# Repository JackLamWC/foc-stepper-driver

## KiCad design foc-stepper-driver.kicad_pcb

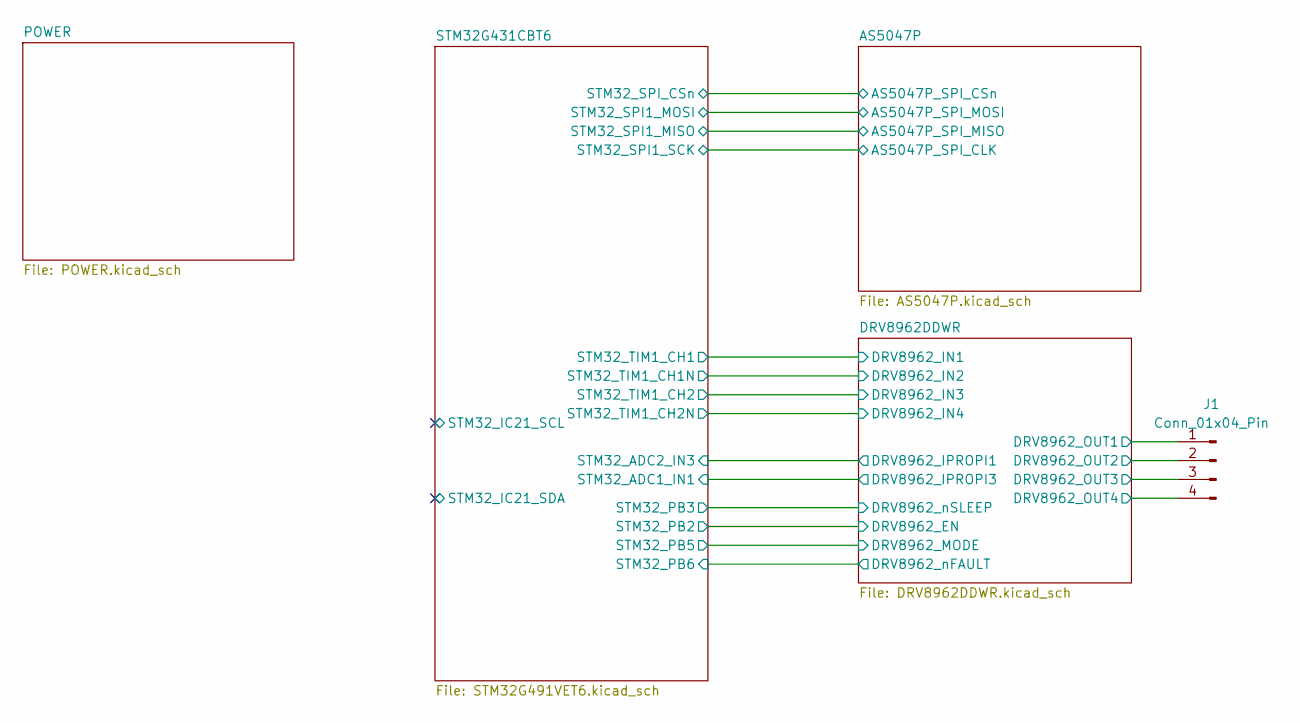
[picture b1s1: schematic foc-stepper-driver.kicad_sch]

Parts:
J1: Conn_01x04_Pin; TerminalBlock_Xinya_XY308-2.54-4P_1x04_P2.54mm_Horizontal

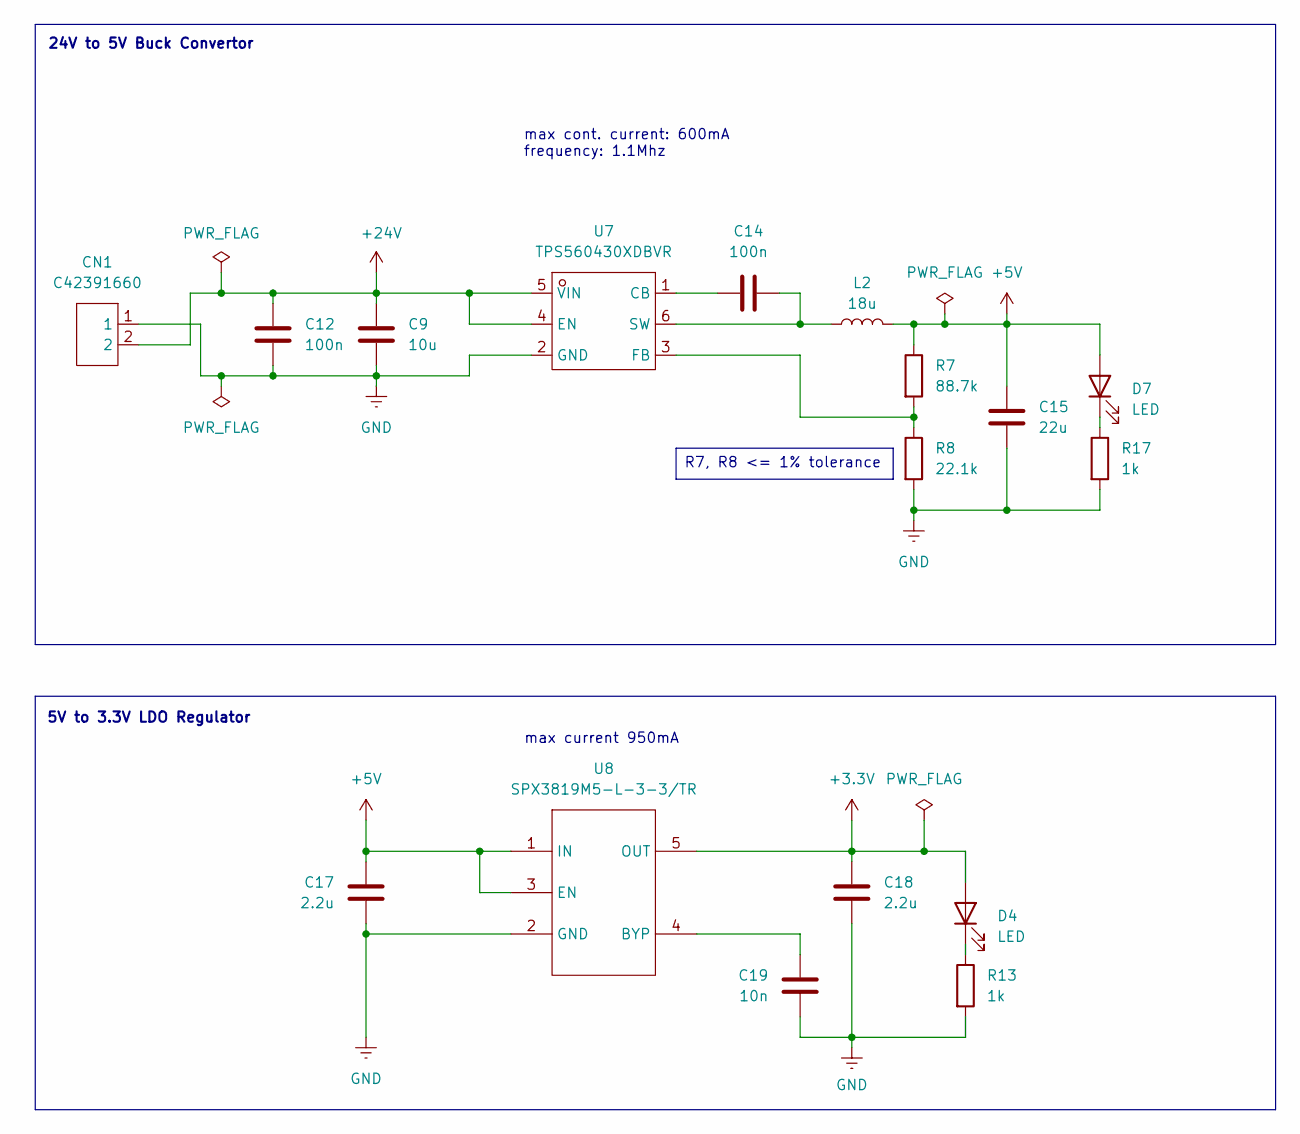
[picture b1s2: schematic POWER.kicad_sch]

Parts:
C9: 10u; C_0402_1005Metric; LCSC C15525
C12, C14: 100n; C_0402_1005Metric; LCSC C91183
C15: 22u; C_0402_1005Metric; LCSC C105226
C17, C18: 2.2u; C_0402_1005Metric; LCSC C12530
C19: 10n; C_0402_1005Metric; LCSC C272878
CN1: C42391660; CONN-TH_2P-P2.50_HX-2.54MM-2P-ZZ-MS; Manufacturer Part HX-XH2.54-2PZZ; LCSC Part Name 1x2P 间距:2.5mm 直插 系列:XH
D4, D7: LED; LED_0603_1608Metric; LCSC C2286
L2: 18u; IND-SMD_L3.0-W3.0_FNR30XXS; LCSC C96895
R7: 88.7k; R_0402_1005Metric; LCSC C25922
R8: 22.1k; R_0603_1608Metric; LCSC C43473
R13, R17: 1k; R_0402_1005Metric; LCSC C11702
U7: TPS560430XDBVR; SOT-23-6_L2.9-W1.6-P0.95-LS2.8-BL; Manufacturer Part TPS560430XDBVR; LCSC Part Name 4V 至 36V、600mA 同步降压转换器
U8: SPX3819M5-L-3-3/TR; SOT-23-5_L3.0-W1.7-P0.95-LS2.8-BL; Manufacturer Part SPX3819M5-L-3-3/TR; LCSC Part Name 输入16V 输出3.3V 500mA

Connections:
+3.3V: C18.2, D4.2 (A), U8.5 (OUT); also elsewhere on the board
+5V: C15.2, C17.2, D7.2 (A), L2.2, R7.1, U8.1 (IN), U8.3 (EN); also elsewhere on the board
+24V: C9.1, C12.1, CN1.2, U7.4 (EN), U7.5 (VIN); also elsewhere on the board
GND: C9.2, C12.2, C15.1, C17.1, C18.1, C19.1, CN1.1, R8.2, R13.2, R17.2, U7.2 (GND), U8.2 (GND); also elsewhere on the board
unnamed: D4.1 (K), R13.1
unnamed: D7.1 (K), R17.1
unnamed: C14.1, U7.1 (CB)
unnamed: R7.2, R8.1, U7.3 (FB)
unnamed: C14.2, L2.1, U7.6 (SW)
unnamed: C19.2, U8.4 (BYP)

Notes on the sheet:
max cont. current: 600mA frequency: 1.1Mhz
5V to 3.3V LDO Regulator
24V to 5V Buck Convertor
max current 950mA
R7, R8 <= 1% tolerance

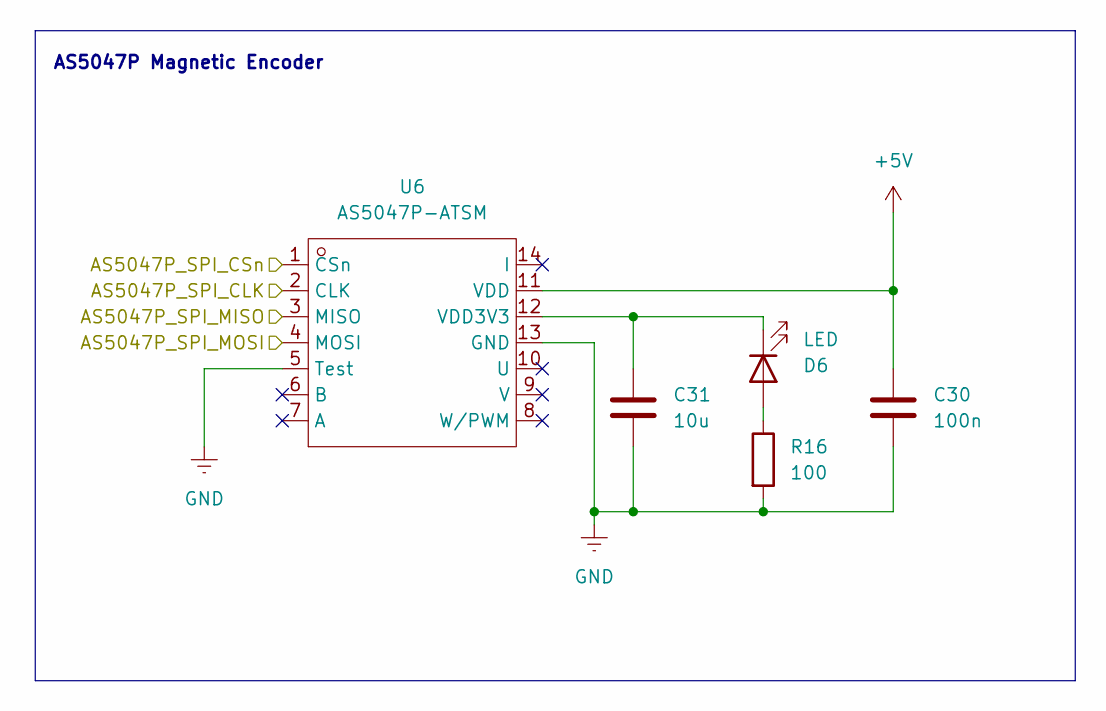
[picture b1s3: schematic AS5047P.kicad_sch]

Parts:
C30: 100n; C_0402_1005Metric
C31: 10u; C_0402_1005Metric
D6: LED; LED_0603_1608Metric
R16: 100; R_0402_1005Metric
U6: AS5047P-ATSM; TSSOP-14_L5.0-W4.4-P0.65-LS6.4-BL; Manufacturer Part AS5047P-ATSM; LCSC Part Name AS5047P-ATSM

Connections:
+5V: C30.1, U6.11 (VDD); also elsewhere on the board
/AS5047P/AS5047P_SPI_CLK: U6.2 (CLK); also elsewhere on the board
/AS5047P/AS5047P_SPI_CSn: U6.1 (CSn); also elsewhere on the board
/AS5047P/AS5047P_SPI_MISO: U6.3 (MISO); also elsewhere on the board
/AS5047P/AS5047P_SPI_MOSI: U6.4 (MOSI); also elsewhere on the board
GND: C30.2, C31.1, R16.2, U6.5 (Test), U6.13 (GND); also elsewhere on the board

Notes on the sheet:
AS5047P Magnetic Encoder

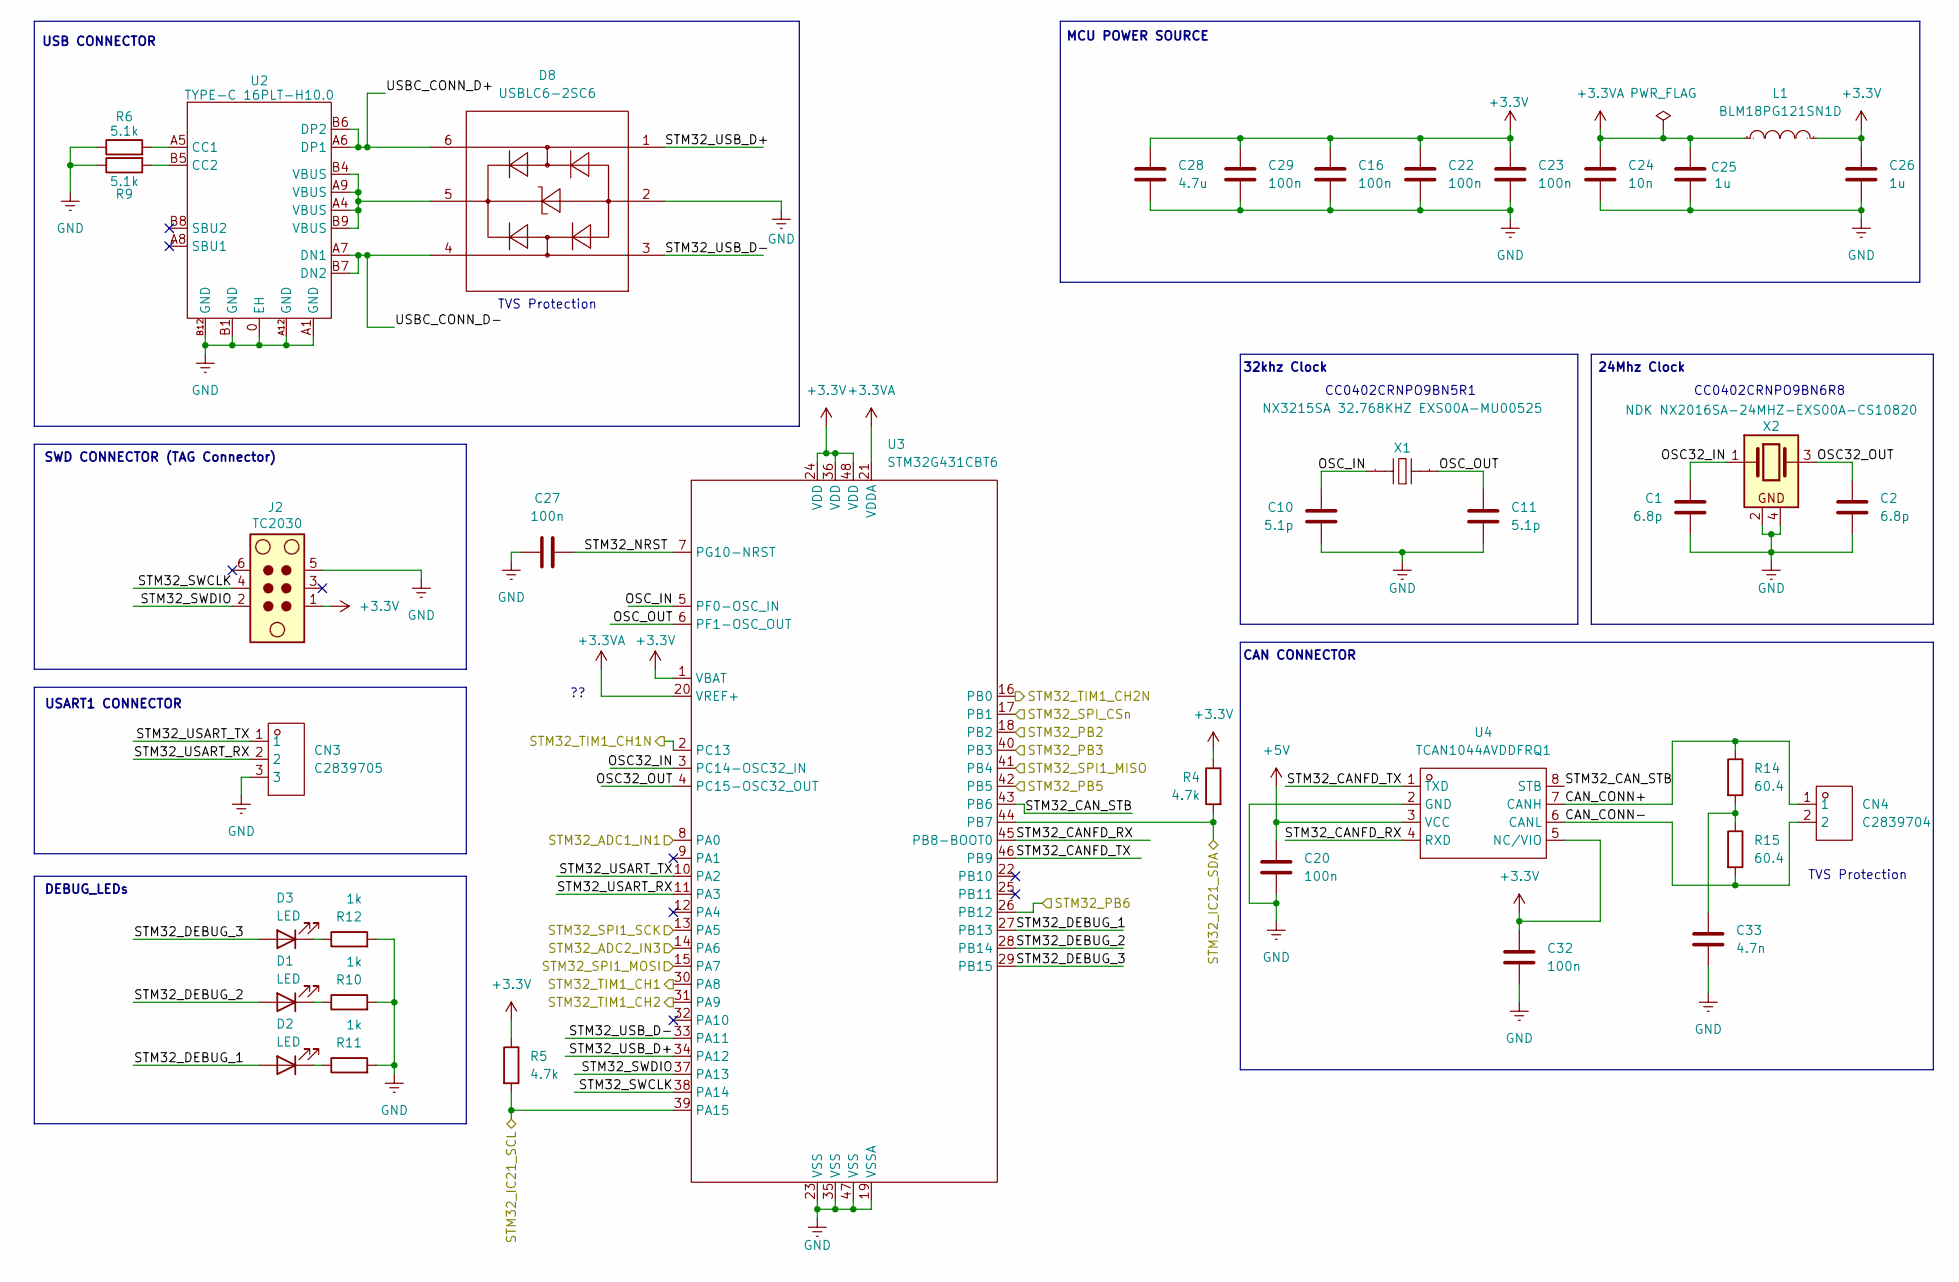
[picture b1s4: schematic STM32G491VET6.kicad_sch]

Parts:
C1, C2: 6.8p; C_0402_1005Metric; LCSC C1864373
C10, C11: 5.1p; C_0402_1005Metric; LCSC C60220
C16, C20, C22, C23, C27, C29, C32: 100n; C_0402_1005Metric; LCSC C91183
C24: 10n; C_0402_1005Metric; LCSC C272878
C25, C26: 1u; C_0402_1005Metric; LCSC C541528
C28: 4.7u; C_0402_1005Metric; LCSC C23687
C33: 4.7n; C_0402_1005Metric; LCSC C1538
CN3: C2839705; CONN-TH_PA-3A; Manufacturer Part PA-3A; LCSC Part Name 1x3P 间距:2mm 直插 系列:PA
CN4: C2839704; CONN-TH_PA-2A; Manufacturer Part PA-2A; LCSC Part Name 1x2P 间距:2mm 直插 系列:PA
D1, D2, D3: LED; LED_0603_1608Metric; LCSC C2286
D8: USBLC6-2SC6; SOT-23-6_L2.9-W1.6-P0.95-LS2.8-BL; Manufacturer Part USBLC6-2SC6; LCSC Part Name 单向ESD
J2: TC2030; Tag-Connect_TC2030-IDC-NL_2x03_P1.27mm_Vertical; LCSC C523739
L1: BLM18PG121SN1D; L0603; Manufacturer Part BLM18PG121SN1D; LCSC Part Name 单路 0603磁珠 阻抗120Ω@100MHz
R4, R5: 4.7k; R_0402_1005Metric; LCSC C25900
R6, R9: 5.1k; R_0402_1005Metric; LCSC C25905
R10, R11, R12: 1k; R_0402_1005Metric; LCSC C11702
R14, R15: 60.4; R_0402_1005Metric; LCSC C166918
U2: TYPE-C 16PLT-H10.0; TYPE-C-SMD_USB4120-03-C; Manufacturer Part TYPE-C 16PLT-H10.0; LCSC Part Name 16P立贴母座
U3: STM32G431CBT6; LQFP-48_L7.0-W7.0-P0.50-LS9.0-BL; Manufacturer Part STM32G431CBT6; LCSC Part Name 带DSP和FPU的170MHz主流ARM Cortex-M4 MCU，具有12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
U4: TCAN1044AVDDFRQ1; TSOT-23-8_L2.9-W1.6-P0.65-LS2.8-BR; Manufacturer Part TCAN1044AVDDFRQ1; LCSC Part Name 具有待机模式和故障保护功能的TCAN1044A-Q1和TCAN1044AV-Q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
X1: NX3215SA 32.768KHZ EXS00A-MU00525; CRYSTAL-SMD_L3.2-W1.5; Manufacturer Part NX3215SA 32.768KHZ EXS00A-MU00525; LCSC Part Name 32.768kHz 6pF
X2: NDK NX2016SA-24MHZ-EXS00A-CS10820; Crystal_SMD_2016-4Pin_2.0x1.6mm; LCSC C6943225

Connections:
+3.3V: C16.1, C22.1, C23.1, C26.1, C28.1, C29.1, C32.1, J2.1, L1.2, R4.1, R5.1, U3.1 (VBAT), U3.24 (VDD), U3.36 (VDD), U3.48 (VDD), U4.5 (NC/VIO); also elsewhere on the board
+3.3VA: C24.1, C25.1, L1.1, U3.20 (VREF+), U3.21 (VDDA); also elsewhere on the board
+5V: C20.1, U4.3 (VCC); also elsewhere on the board
/AS5047P/AS5047P_SPI_CLK: U3.13 (PA5); also elsewhere on the board
/AS5047P/AS5047P_SPI_CSn: U3.17 (PB1); also elsewhere on the board
/AS5047P/AS5047P_SPI_MISO: U3.41 (PB4); also elsewhere on the board
/AS5047P/AS5047P_SPI_MOSI: U3.15 (PA7); also elsewhere on the board
/DRV8962DDWR/DRV8962_EN: U3.18 (PB2); also elsewhere on the board
/DRV8962DDWR/DRV8962_IN1: U3.30 (PA8); also elsewhere on the board
/DRV8962DDWR/DRV8962_IN2: U3.2 (PC13); also elsewhere on the board
/DRV8962DDWR/DRV8962_IN3: U3.16 (PB0); also elsewhere on the board
/DRV8962DDWR/DRV8962_IN4: U3.31 (PA9); also elsewhere on the board
/DRV8962DDWR/DRV8962_IPROPI1: U3.8 (PA0); also elsewhere on the board
/DRV8962DDWR/DRV8962_IPROPI3: U3.14 (PA6); also elsewhere on the board
/DRV8962DDWR/DRV8962_MODE: U3.42 (PB5); also elsewhere on the board
/DRV8962DDWR/DRV8962_nFAULT: U3.26 (PB12); also elsewhere on the board
/DRV8962DDWR/DRV8962_nSLEEP: U3.40 (PB3); also elsewhere on the board
/STM32G431CBT6/CAN_CONN+: CN4.1, R14.1, U4.7 (CANH)
/STM32G431CBT6/CAN_CONN-: CN4.2, R15.2, U4.6 (CANL)
/STM32G431CBT6/OSC32_IN: C1.1, U3.3 (PC14-OSC32_IN), X2.1
/STM32G431CBT6/OSC32_OUT: C2.1, U3.4 (PC15-OSC32_OUT), X2.3
/STM32G431CBT6/OSC_IN: C10.1, U3.5 (PF0-OSC_IN), X1.2
/STM32G431CBT6/OSC_OUT: C11.1, U3.6 (PF1-OSC_OUT), X1.1
/STM32G431CBT6/STM32_CANFD_RX: U3.45 (PB8-BOOT0), U4.4 (RXD)
/STM32G431CBT6/STM32_CANFD_TX: U3.46 (PB9), U4.1 (TXD)
/STM32G431CBT6/STM32_CAN_STB: U3.43 (PB6), U4.8 (STB)
/STM32G431CBT6/STM32_DEBUG_1: D2.2 (A), U3.27 (PB13)
/STM32G431CBT6/STM32_DEBUG_2: D1.2 (A), U3.28 (PB14)
/STM32G431CBT6/STM32_DEBUG_3: D3.2 (A), U3.29 (PB15)
/STM32G431CBT6/STM32_IC21_SCL: R5.2, U3.39 (PA15)
/STM32G431CBT6/STM32_IC21_SDA: R4.2, U3.44 (PB7)
/STM32G431CBT6/STM32_NRST: C27.2, U3.7 (PG10-NRST)
/STM32G431CBT6/STM32_SWCLK: J2.4, U3.38 (PA14)
/STM32G431CBT6/STM32_SWDIO: J2.2, U3.37 (PA13)
/STM32G431CBT6/STM32_USART_RX: CN3.2, U3.11 (PA3)
/STM32G431CBT6/STM32_USART_TX: CN3.1, U3.10 (PA2)
/STM32G431CBT6/STM32_USB_D+: D8.1, U3.34 (PA12)
/STM32G431CBT6/STM32_USB_D-: D8.3, U3.33 (PA11)
/STM32G431CBT6/USBC_CONN_D+: D8.6, U2.A6 (DP1), U2.B6 (DP2)
/STM32G431CBT6/USBC_CONN_D-: D8.4, U2.A7 (DN1), U2.B7 (DN2)
GND: C1.2, C2.2, C10.2, C11.2, C16.2, C20.2, C22.2, C23.2, C24.2, C25.2, C26.2, C27.1, C28.2, C29.2, C32.2, C33.2, CN3.3, D8.2, J2.5, R6.1, R9.1, R10.2, R11.2, R12.2, U2.0 (EH), U2.A1 (GND), U2.A12 (GND), U2.B1 (GND), U2.B12 (GND), U3.19 (VSSA), U3.23 (VSS), U3.35 (VSS), U3.47 (VSS), U4.2 (GND), X2.2, X2.4; also elsewhere on the board
unnamed: C33.1, R14.2, R15.1
unnamed: D1.1 (K), R10.1
unnamed: D2.1 (K), R11.1
unnamed: D3.1 (K), R12.1
unnamed: D8.5, U2.A4 (VBUS), U2.A9 (VBUS), U2.B4 (VBUS), U2.B9 (VBUS)
unnamed: R6.2, U2.A5 (CC1)
unnamed: R9.2, U2.B5 (CC2)

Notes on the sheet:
DEBUG_LEDs
CC0402CRNPO9BN5R1
CC0402CRNPO9BN6R8
TVS Protection
CAN CONNECTOR
SWD CONNECTOR (TAG Connector)
USB CONNECTOR
MCU POWER SOURCE
32khz Clock
USART1 CONNECTOR
24Mhz Clock

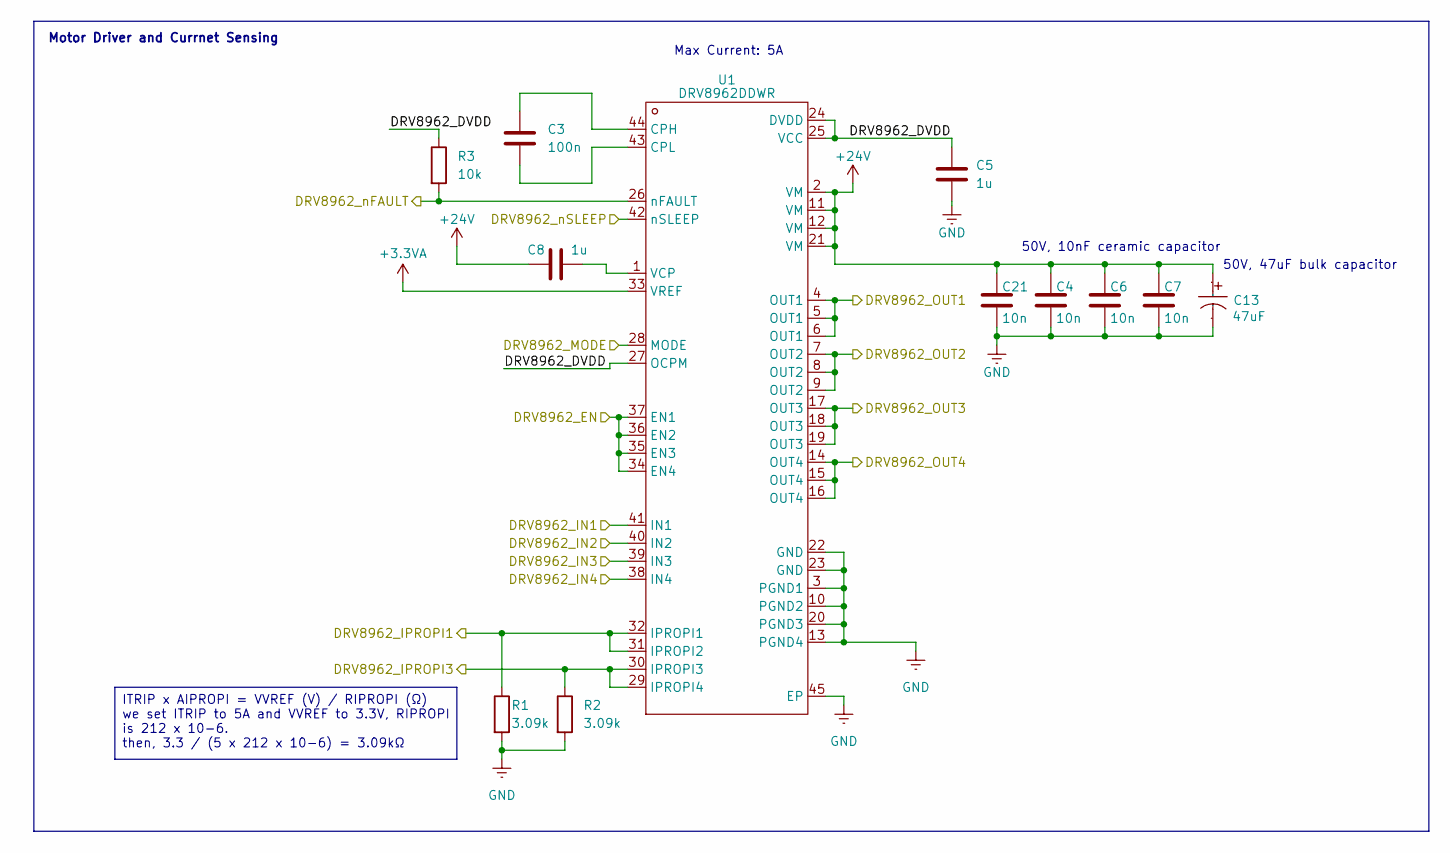
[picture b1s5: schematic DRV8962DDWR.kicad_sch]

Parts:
C3: 100n; C_0402_1005Metric; LCSC C91183
C4, C6, C7, C21: 10n; C_0402_1005Metric; LCSC C272878
C5, C8: 1u; C_0402_1005Metric; LCSC C541528
C13: 47uF; CAP-SMD_BD6.3-L6.6-W6.6-LS7.6-FD; Manufacturer Part RVT1H470M0607; LCSC Part Name 47uF ±20% 50V
R1, R2: 3.09k; R_0402_1005Metric; LCSC C11460
R3: 10k; R_0805_2012Metric; LCSC C25744
U1: DRV8962DDWR; HTSSOP-44_L14.0-W6.1-P0.64-LS8.1-BL-EP-2; Manufacturer Part DRV8962DDWR; LCSC Part Name 四通道半桥驱动器，带电流感应输出

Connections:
+3.3VA: U1.33 (VREF); also elsewhere on the board
+24V: C4.1, C6.1, C7.1, C8.1, C13.1, C21.1, U1.2 (VM), U1.11 (VM), U1.12 (VM), U1.21 (VM); also elsewhere on the board
/DRV8962DDWR/DRV8962_DVDD: C5.1, R3.1, U1.24 (DVDD), U1.25 (VCC), U1.27 (OCPM)
/DRV8962DDWR/DRV8962_EN: U1.34 (EN4), U1.35 (EN3), U1.36 (EN2), U1.37 (EN1); also elsewhere on the board
/DRV8962DDWR/DRV8962_IN1: U1.41 (IN1); also elsewhere on the board
/DRV8962DDWR/DRV8962_IN2: U1.40 (IN2); also elsewhere on the board
/DRV8962DDWR/DRV8962_IN3: U1.39 (IN3); also elsewhere on the board
/DRV8962DDWR/DRV8962_IN4: U1.38 (IN4); also elsewhere on the board
/DRV8962DDWR/DRV8962_IPROPI1: R1.1, U1.31 (IPROPI2), U1.32 (IPROPI1); also elsewhere on the board
/DRV8962DDWR/DRV8962_IPROPI3: R2.1, U1.29 (IPROPI4), U1.30 (IPROPI3); also elsewhere on the board
/DRV8962DDWR/DRV8962_MODE: U1.28 (MODE); also elsewhere on the board
/DRV8962DDWR/DRV8962_OUT1: U1.4 (OUT1), U1.5 (OUT1), U1.6 (OUT1); also elsewhere on the board
/DRV8962DDWR/DRV8962_OUT2: U1.7 (OUT2), U1.8 (OUT2), U1.9 (OUT2); also elsewhere on the board
/DRV8962DDWR/DRV8962_OUT3: U1.17 (OUT3), U1.18 (OUT3), U1.19 (OUT3); also elsewhere on the board
/DRV8962DDWR/DRV8962_OUT4: U1.14 (OUT4), U1.15 (OUT4), U1.16 (OUT4); also elsewhere on the board
/DRV8962DDWR/DRV8962_nFAULT: R3.2, U1.26 (nFAULT); also elsewhere on the board
/DRV8962DDWR/DRV8962_nSLEEP: U1.42 (nSLEEP); also elsewhere on the board
GND: C4.2, C5.2, C6.2, C7.2, C13.2, C21.2, R1.2, R2.2, U1.3 (PGND1), U1.10 (PGND2), U1.13 (PGND4), U1.20 (PGND3), U1.22 (GND), U1.23 (GND), U1.45 (EP); also elsewhere on the board
unnamed: C3.1, U1.44 (CPH)
unnamed: C3.2, U1.43 (CPL)
unnamed: C8.2, U1.1 (VCP)

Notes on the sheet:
50V, 47uF bulk capacitor
Motor Driver and Currnet Sensing
Max Current: 5A
50V, 10nF ceramic capacitor
ITRIP x AIPROPI = VVREF (V) / RIPROPI (Ω) we set ITRIP to 5A and VVREF to 3.3V, RIPROPI is 212 x 10-6. then, 3.3 / (5 x 212 x 10-6) = 3.09kΩ

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
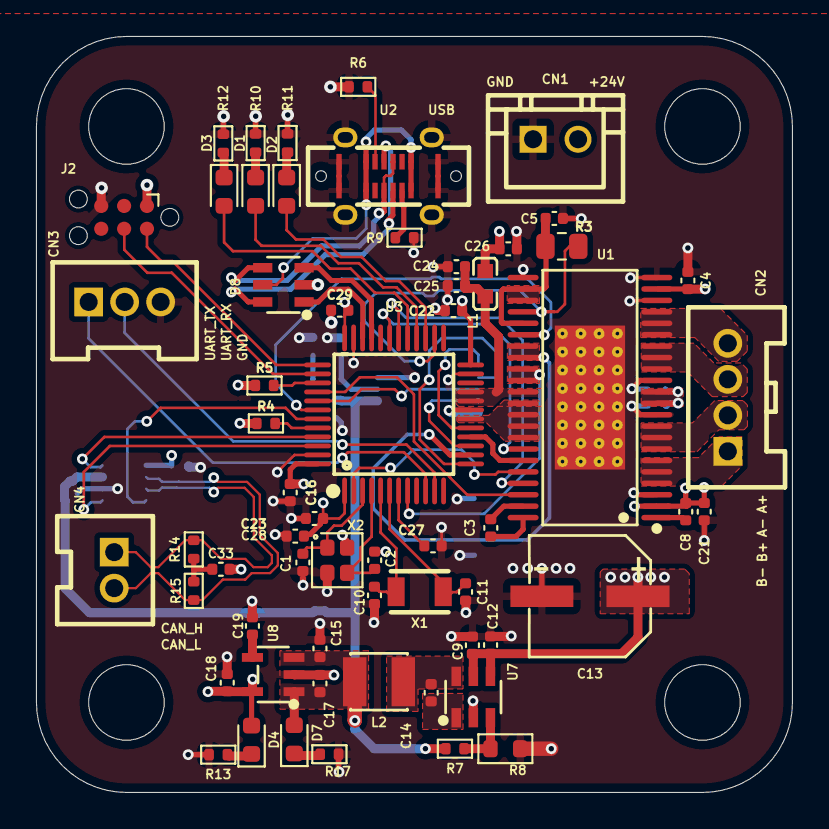
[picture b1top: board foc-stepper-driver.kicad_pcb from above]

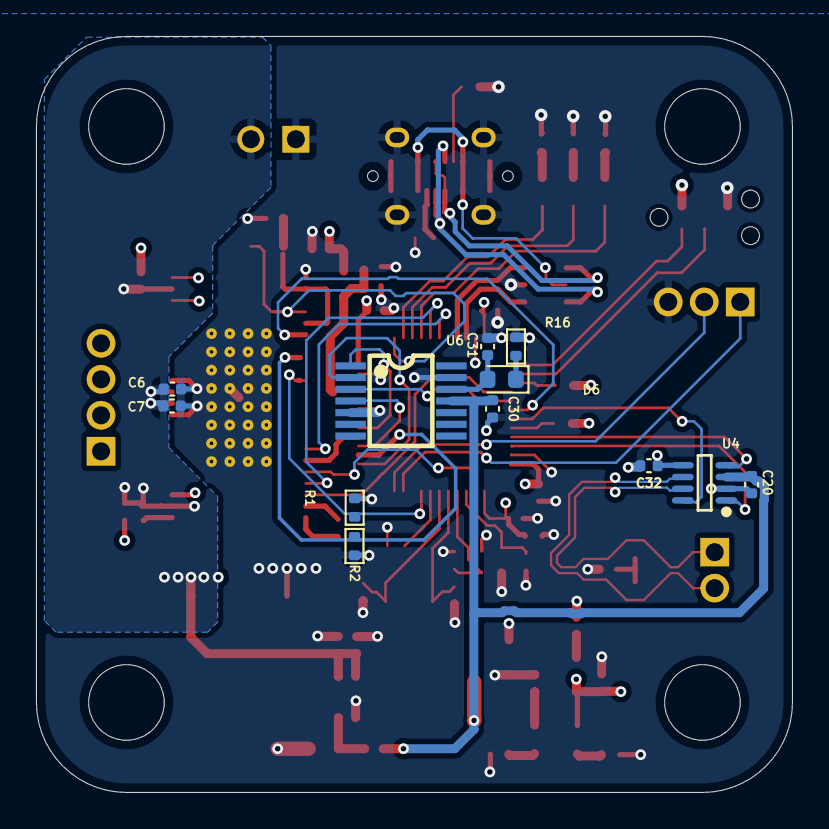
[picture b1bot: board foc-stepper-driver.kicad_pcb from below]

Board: 4 copper layers, 42.0 x 42.0 mm, 73 parts (12 on the bottom side), 65 nets.

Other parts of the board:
CN2: C2839706; CONN-TH_PA-4A

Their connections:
/DRV8962DDWR/DRV8962_OUT1: CN2.1; also elsewhere on the board
/DRV8962DDWR/DRV8962_OUT2: CN2.2; also elsewhere on the board
/DRV8962DDWR/DRV8962_OUT3: CN2.4; also elsewhere on the board
/DRV8962DDWR/DRV8962_OUT4: CN2.3; also elsewhere on the board

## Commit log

2026-04-13 init commit
2026-04-13 add git ignore
2026-04-13 add pd power
2026-04-14 feat: add as5047p
2026-04-15 feat: add can and usart connector
2026-05-01 change components
2026-05-03 update sch
2026-05-08 pcb layout
2026-05-08 update route
2026-05-08 update zone
2026-05-12 update trace width
